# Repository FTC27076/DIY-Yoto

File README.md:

# DIY Yoto

A screen-free, kid-friendly audio player in the style of a Yoto. Put a card on top and it plays that card's stories or songs. It runs fully offline: no Wi-Fi, no app, no account. All audio lives on a micro SD card, and any 13.56 MHz RFID card or NFC sticker can become a card.

## Features

- Tap a card to play, lift it to pause, put it back to resume where it stopped
- Each card remembers which track it was on
- Two knobs: volume (press to pause) and track skip (press to restart the track)
- Volume cap for small ears
- Rechargeable LiPo with USB-C charging; play while charging
- Deep sleep after 5 minutes idle, wake with either knob
- Low-battery warning and safe shutdown

## Hardware

| Part | What it does |
|---|---|
| ESP32-S3-WROOM-1 (SMD) | Main controller |
| RC522 RFID reader | Reads the cards |
| Adafruit MAX98357A (#3006) | I2S amplifier, drives a 4–8 Ω 3 W speaker |
| Adafruit micro SD breakout (#4682) | Audio storage, 4-bit SDIO |
| TP4056 USB-C module (with protection) | Charges and protects the battery |
| MT3608 boost module | 5 V for the amp (set to 5.0 V before connecting!) |
| MCP1825S-3302E/AB (TO-220) | 3.3 V regulator for the logic |
| 2× EC11 rotary encoders | Volume and track controls |
| USB-C (J16) | Programming and Serial Monitor only |
| 3.7 V 2000 mAh LiPo (Adafruit #2011) | Power |

Everything except the ESP32 module is through-hole or a module on headers, so it's hand-solderable.
## BILL OF MATERIALS

Costs are in USD for one player. Most unit prices are estimates, so check them in each cart.

| Item | Qty | Supplier | Cost/item | Total Cost | link |
|---|---:|---|---:|---:|---|
| U2 – ESP32-S3-WROOM-1-N8R8 module (Espressif) | 1 | DigiKey | $4.50 | $4.50 | [link](https://www.digikey.ca/en/products/detail/espressif-systems/ESP32-S3-WROOM-1-N8R8/15295891) |
| U1 – MCP1825S-3302E/AB 3.3V LDO, TO-220 (Microchip) | 1 | DigiKey | $1.75 | $1.75 | [link](https://www.digikey.ca/en/products/result?keywords=MCP1825S-3302E%2FAB) |
| R1, R2 – 100k 1/4W resistor (Stackpole CF14JT100K, cut tape) | 2 | DigiKey | $0.10 | $0.20 | [link](https://www.digikey.ca/en/products/result?keywords=CF14JT100K) |
| R3–R8 – 10k 1/4W resistor (Stackpole CF14JT10K0, cut tape) | 6 | DigiKey | $0.10 | $0.60 | [link](https://www.digikey.ca/en/products/result?keywords=CF14JT10K0) |
| R9, R10 – 5.1k 1/4W resistor (Stackpole CF14JT5K10, cut tape) | 2 | DigiKey | $0.10 | $0.20 | [link](https://www.digikey.ca/en/products/detail/stackpole-electronics-inc/CF14JT5K10/1830367) |
| C1, C5 – 100µF 16V electrolytic (Panasonic EEU-FR1C101) | 2 | DigiKey | $0.40 | $0.80 | [link](https://www.digikey.ca/en/products/detail/panasonic-industry/EEU-FR1C101/2433525) |
| C2, C3, C9 – 10µF 25V ceramic, 5mm pitch (TDK FG28X5R1E106MRT06) | 3 | LCSC / JLC | $0.20 | $0.60 | [link](https://www.lcsc.com/product-detail/C1620216.html) |
| C4, C6, C7, C10 – 100nF 50V ceramic (KNSCHA 178MU0006) | 4 | LCSC / JLC | $0.03 | $0.12 | [link](https://www.lcsc.com/product-detail/C5632430.html) |
| C8 – 1µF 50V ceramic (KNSCHA 178MU0010) | 1 | LCSC / JLC | $0.05 | $0.05 | [link](https://www.lcsc.com/product-detail/C5632434.html) |
| SW2, SW3 – 6x6mm tactile switch, reset/boot (Omron B3F-1000) | 2 | DigiKey | $0.35 | $0.70 | [link](https://www.digikey.ca/en/products/detail/omron-electronics-inc-emc-div/B3F-1000/33150) |
| SW4, SW5 – rotary encoder with switch (Alps EC11E15244G1) | 2 | LCSC / JLC | $1.50 | $3.00 | [link](https://www.lcsc.com/product-detail/C370970.html) |
| J16 – USB-C receptacle, 16-pin (HRO TYPE-C-31-M-12) | 1 | LCSC / JLC | $0.25 | $0.25 | [link](https://www.lcsc.com/product-detail/C165948.html) |
| J3 – JST-PH 2-pin side-entry socket, battery (JST S2B-PH-K-S) | 1 | LCSC / JLC | $0.10 | $0.10 | [link](https://www.lcsc.com/product-detail/C173752.html) |
| J7 – JST-XH 2-pin socket, power switch (JST B2B-XH-A) | 1 | LCSC / JLC | $0.05 | $0.05 | [link](https://www.lcsc.com/product-detail/C158012.html) |
| MOD1 – 1x8 2.54mm female header (BOOMELE) | 1 | LCSC / JLC | $0.10 | $0.10 | [link](https://www.lcsc.com/product-detail/C27438.html) |
| J12 (M1) – TP4056 USB-C charger module with protection (pack of 5) | 1 | Amazon | $8.00 | $8.00 | [link](https://www.amazon.ca/s?k=TP4056+type-c+protection+module) |
| J13 (M2) – MT3608 boost module (pack of 5) | 1 | Amazon | $8.00 | $8.00 | [link](https://www.amazon.ca/s?k=MT3608+boost+module) |
| J14 (M3) – Adafruit MAX98357A I2S amp breakout (3006) | 1 | DigiKey | $5.95 | $5.95 | [link](https://www.digikey.ca/en/products/detail/adafruit-industries-llc/3006/6058477) |
| J15 (M4) – Adafruit micro SD SPI/SDIO breakout (4682) | 1 | DigiKey | $3.50 | $3.50 | [link](https://www.digikey.ca/en/products/detail/adafruit-industries-llc/4682/12822319) |
| MOD1 – RC522 RFID reader kit with card + fob (ProtoSupplies) | 1 | ProtoSupplies | $2.59 | $2.59 | [link](https://protosupplies.com/product/mfrc522-rfid-reader-key-card-and-key-ring/) |
| Header pins for M1/M2 – 1x40 break-away male header (BOOMELE) | 1 | LCSC / JLC | $0.15 | $0.15 | [link](https://www.lcsc.com/product-detail/C2337.html) |
| LiPo battery 3.7V 2000mAh with JST-PH (Adafruit 2011) | 1 | DigiKey | $12.50 | $12.50 | [link](https://www.digikey.ca/en/products/detail/adafruit-industries-llc/2011/6612469) |
| Speaker 40mm 4Ω 3W (Adafruit 3968) | 1 | DigiKey | $4.95 | $4.95 | [link](https://www.digikey.ca/en/products/detail/adafruit-industries-llc/3968/9745251) |
| Power switch – SPDT panel toggle 5A (E-Switch 100SP1T1B1M2QEH) | 1 | DigiKey | $4.50 | $4.50 | [link](https://www.digikey.ca/en/products/detail/e-switch/100SP1T1B1M2QEH/378821) |
| RFID cards – MIFARE Classic 1K (Adafruit 359) | 5 | DigiKey | $1.95 | $9.75 | [link](https://www.digikey.ca/en/products/detail/adafruit-industries-llc/359/5353589) |
| micro SD card 16–32GB (SanDisk / Samsung) | 1 | Amazon | $8.00 | $8.00 | [link](https://www.amazon.ca/s?k=sandisk+32gb+microsd) |
| Optional – JST-XH plug housing for J7 (JST XHP-2) | 0 | DigiKey | $0.10 | $0.00 | [link](https://www.digikey.ca/en/products/detail/jst-sales-america-inc/XHP-2/555485) |
| Optional – JST-XH crimp contacts (JST SXH-001T-P0.6, cut tape) | 0 | DigiKey | $0.10 | $0.00 | [link](https://www.digikey.ca/en/products/detail/jst-sales-america-inc/SXH-001T-P0.6/455-1135-1-ND/527370) |
| Parts subtotal | | | | $80.91 | |
| Tax (Ontario HST 13%) | | | | $13.77 | |
| **Grand total (USD)** | | | | **~$119.68** | |

### Pin map

| Function | GPIO |
|---|---|
| I2S BCLK / LRC / DIN | 5 / 6 / 7 |
| Amp enable (SD_MODE) | 8 |
| RC522 RST / SS / MOSI / SCK / MISO | 9 / 10 / 11 / 12 / 13 |
| SD CMD / CLK / D0 / D1 / D2 / D3 | 14 / 39 / 40 / 41 / 42 / 21 |
| Volume encoder A / B / push | 15 / 16 / 17 |
| Track encoder A / B / push | 18 / 4 / 2 |
| Battery sense (100k/100k divider) | 1 |
| USB D− / D+ | 19 / 20 |

## Repository contents

| Path | What's in it |
|---|---|
| `DiyYoto/DiyYoto.ino` | Arduino firmware |
| `DiyYoto/README.md` | Full firmware setup, SD card layout, controls and troubleshooting |
| `DiyYoto.pretty/` | Custom KiCad footprints for the four modules |
| `make_footprints.py` | Regenerates those footprints |

## Quick start

1. **Build the board.** Order the PCB, solder the parts, and set the MT3608 to 5.0 V with a multimeter *before* plugging in the amp.
2. **Flash the firmware.** In Arduino IDE 2, install the ESP32 core plus the MFRC522 and ESP32-audioI2S libraries. Set Board to *ESP32S3 Dev Module*, USB CDC On Boot to *Enabled*, and PSRAM to match your module. Switch the player on, plug USB into J16, hold BOOT, tap RESET, release BOOT, then upload.
3. **Prepare the SD card.** Format it FAT32 and create a `/cards` folder.
4. **Add a card.** Tap a blank card. The player creates `/cards/<card UID>/`. Copy MP3s into that folder (they play in alphabetical order), put the SD card back, and tap again.

## Images of final design

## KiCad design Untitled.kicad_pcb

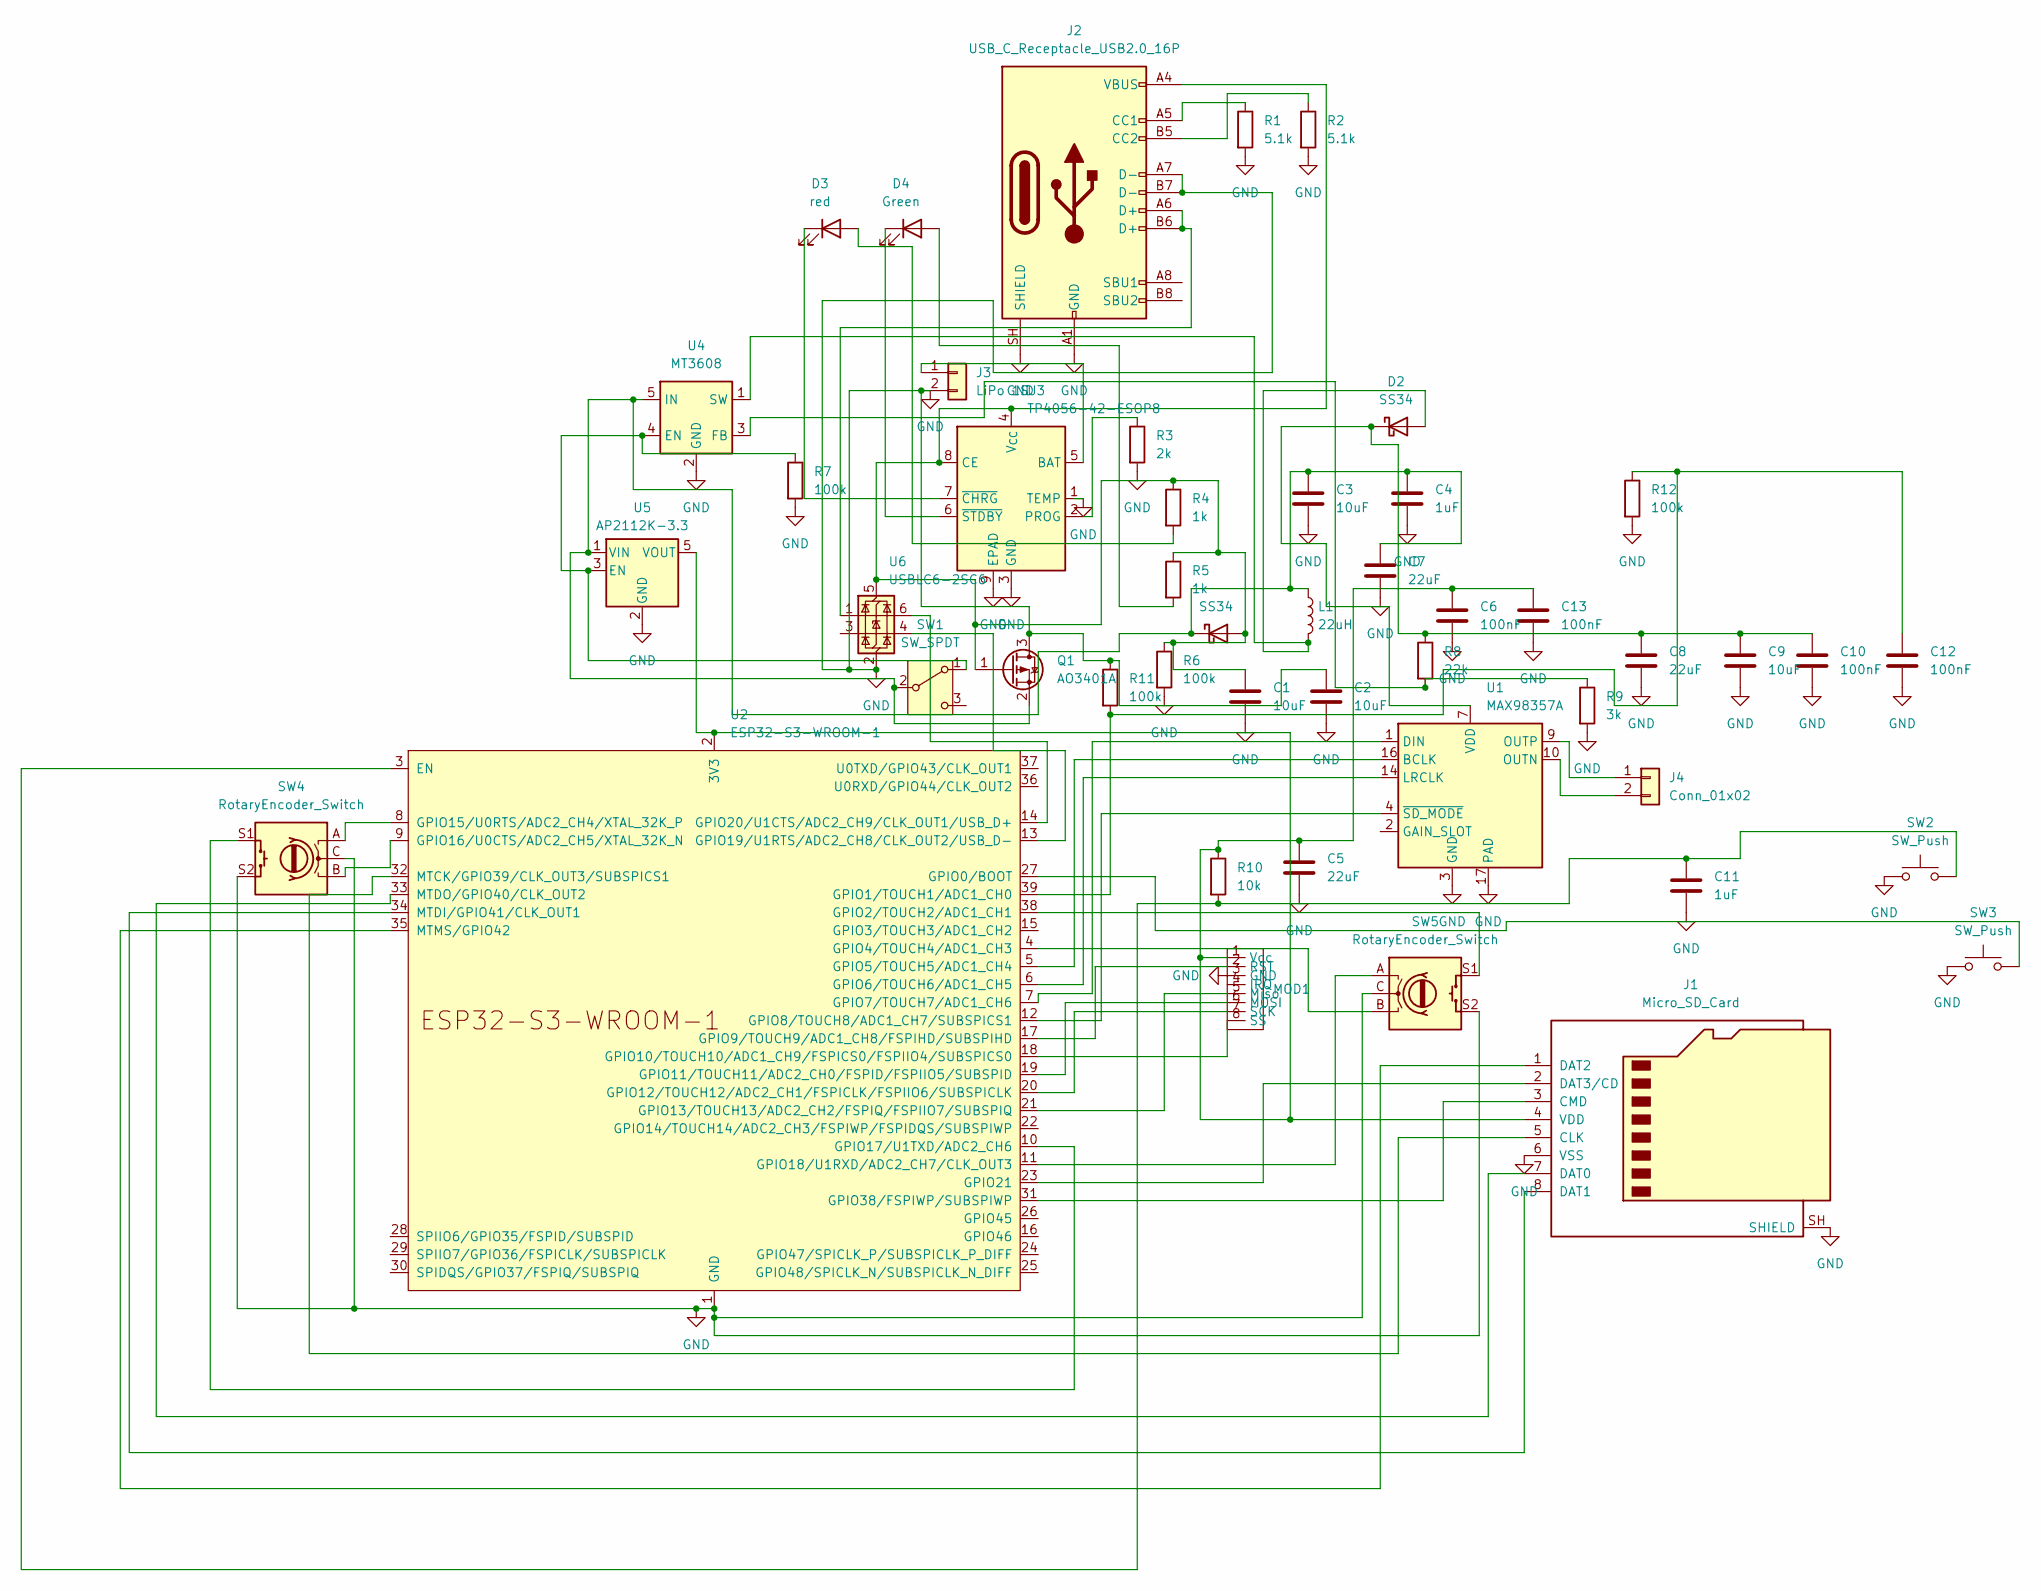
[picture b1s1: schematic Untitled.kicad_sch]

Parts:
C1, C2, C3, C9: 10uF; C_0603_1608Metric
C4, C11: 1uF; C_0603_1608Metric
C5, C7, C8: 22uF; C_0603_1608Metric
C6, C10, C12, C13: 100nF; C_0603_1608Metric
D1, D2: SS34; D_SMA
D3: red; LED_0805_2012Metric
D4: Green; LED_0805_2012Metric
J1: Micro_SD_Card; microSD_HC_Molex_104031-0811
J2: USB_C_Receptacle_USB2.0_16P; USB_C_Receptacle_HRO_TYPE-C-31-M-12
J3: LiPo 1S; JST_PH_S2B-PH-K_1x02_P2.00mm_Horizontal
J4: Conn_01x02; JST_PH_S2B-PH-K_1x02_P2.00mm_Horizontal
L1: 22uH; L_Bourns_SRN6045TA
MOD1: PinSocket_1x08_P2.54mm_Vertical
Q1: AO3401A; SOT-23
R1, R2: 5.1k; R_0603_1608Metric
R3: 2k; R_0603_1608Metric
R4, R5: 1k; R_0603_1608Metric
R6, R7, R11, R12: 100k; R_0603_1608Metric
R8: 22k; R_0603_1608Metric
R9: 3k; R_0603_1608Metric
R10: 10k; R_0603_1608Metric
SW1: SW_SPDT; SW_SPDT_PCM12
SW2, SW3: SW_Push; SW_SPST_TL3342
SW4, SW5: RotaryEncoder_Switch; RotaryEncoder_Alps_EC12E-Switch_Vertical_H20mm
U1: MAX98357A; TQFN-16-1EP_3x3mm_P0.5mm_EP1.23x1.23mm
U2: ESP32-S3-WROOM-1; ESP32-S3-WROOM-1ThermalVia0.3
U3: TP4056-42-ESOP8; SOIC-8-1EP_3.9x4.9mm_P1.27mm_EP2.41x3.3mm
U4: MT3608; SOT-23-6
U5: AP2112K-3.3; SOT-23-5
U6: USBLC6-2SC6; SOT-23-6

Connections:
GND: C1.2, C2.1, C2.2, C3.2, C4.2, C5.2, C6.2, C7.2, C8.2, C9.2, C10.2, C11.2, C12.2, C13.2, J1.6 (VSS), J1.SH (SHIELD), J2.A1 (GND), J2.A7 (D-), J2.A12 (GND), J2.B1 (GND), J2.B7 (D-), J2.B12 (GND), J2.SH (SHIELD), J3.2, MOD1.3 (GND), Q1.3 (D), R1.2, R2.2, R3.2, R6.2, R7.2, R9.2, R11.1, R12.2, SW2.1, SW3.1, SW4.C, SW4.S2, SW5.C, SW5.S2, U1.3 (GND), U1.11 (GND), U1.15 (GND), U1.17 (PAD), U2.1 (GND), U2.40 (GND), U2.41 (GND), U3.1 (TEMP), U3.3 (GND), U3.9 (EPAD), U4.2 (GND), U5.2 (GND), U6.2 (GND)
unnamed: C1.1, D1.2 (A), J2.A4 (VBUS), J2.A9 (VBUS), J2.B4 (VBUS), J2.B9 (VBUS), Q1.1 (G), R4.1, R5.1, R6.1, U3.4 (V_{CC}), U3.8 (CE), U6.5 (VBUS)
unnamed: C3.1, C4.1, C7.1, D1.1 (K), L1.1, Q1.2 (S), SW1.2 (B), U4.5 (IN), U5.1 (VIN)
unnamed: D2.2 (A), L1.2, U4.1 (SW)
unnamed: C8.1, C9.1, C10.1, D2.1 (K), R8.1, U1.7 (VDD), U1.8 (VDD)
unnamed: D3.2 (A), R4.2
unnamed: D3.1 (K), U3.7 (~CHRG)
unnamed: D4.2 (A), R5.2
unnamed: D4.1 (K), U3.6 (~STDBY)
unnamed: J1.5 (CLK), U2.32 (MTCK/GPIO39/CLK_OUT3/SUBSPICS1)
unnamed: J1.3 (CMD), U2.31 (GPIO38/FSPIWP/SUBSPIWP)
unnamed: J1.7 (DAT0), U2.33 (MTDO/GPIO40/CLK_OUT2)
unnamed: J1.8 (DAT1), U2.34 (MTDI/GPIO41/CLK_OUT1)
unnamed: J1.1 (DAT2), U2.35 (MTMS/GPIO42)
unnamed: J1.2 (DAT3/CD), U2.23 (GPIO21)
unnamed: C5.1, C6.1, C13.1, J1.4 (VDD), MOD1.1 (Vcc), R10.1, U2.2 (3V3), U5.5 (VOUT)
unnamed: J2.A5 (CC1), R1.1
unnamed: J2.B5 (CC2), R2.1
unnamed: J2.A6 (D+), J2.B6 (D+), U6.1 (I/O1)
unnamed: J3.1, U3.5 (BAT)
unnamed: J4.1, U1.9 (OUTP)
unnamed: J4.2, U1.10 (OUTN)
unnamed: MOD1.6 (MOSI), U2.19 (GPIO11/TOUCH11/ADC2_CH0/FSPID/FSPIIO5/S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)
unnamed: MOD1.5 (Miso), U2.21 (GPIO13/TOUCH13/ADC2_CH2/FSPIQ/FSPIIO7/S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)
unnamed: MOD1.2 (RST), U2.17 (GPIO9/TOUCH9/ADC1_CH8/FSPIHD/SUBSPIHD)
unnamed: MOD1.7 (SCK), U2.20 (GPIO12/TOUCH12/ADC2_CH1/FSPICLK/FSPIIO6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)
unnamed: MOD1.8 (SS), U2.18 (GPIO10/TOUCH10/ADC1_CH9/FSPICS0/FSPIIO4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)
unnamed: R7.1, SW1.1 (A), U4.4 (EN), U5.3 (EN)
unnamed: U1.16 (BCLK), U2.5 (GPIO5/TOUCH5/ADC1_CH4)
unnamed: U1.1 (DIN), U2.7 (GPIO7/TOUCH7/ADC1_CH6)
unnamed: U1.14 (LRCLK), U2.6 (GPIO6/TOUCH6/ADC1_CH5)
unnamed: U1.4 (~SD_MODE), U2.12 (GPIO8/TOUCH8/ADC1_CH7/SUBSPICS1)
unnamed: C11.1, R10.2, SW2.2, U2.3 (EN)
unnamed: SW3.2, U2.27 (GPIO0/BOOT)
unnamed: C12.1, R11.2, R12.1, U2.39 (GPIO1/TOUCH1/ADC1_CH0)
unnamed: SW5.S1, U2.38 (GPIO2/TOUCH2/ADC1_CH1)
unnamed: SW5.B, U2.4 (GPIO4/TOUCH4/ADC1_CH3)
unnamed: SW4.A, U2.8 (GPIO15/U0RTS/ADC2_CH4/XTAL_32K_P)
unnamed: SW4.B, U2.9 (GPIO16/U0CTS/ADC2_CH5/XTAL_32K_N)
unnamed: SW4.S1, U2.10 (GPIO17/U1TXD/ADC2_CH6)
unnamed: SW5.A, U2.11 (GPIO18/U1RXD/ADC2_CH7/CLK_OUT3)
unnamed: U2.13 (GPIO19/U1RTS/ADC2_CH8/CLK_OUT2/USB_D-), U6.4 (I/O2)
unnamed: U2.14 (GPIO20/U1CTS/ADC2_CH9/CLK_OUT1/USB_D+), U6.6 (I/O1)
unnamed: R3.1, U3.2 (PROG)
unnamed: R8.2, R9.1, U4.3 (FB)

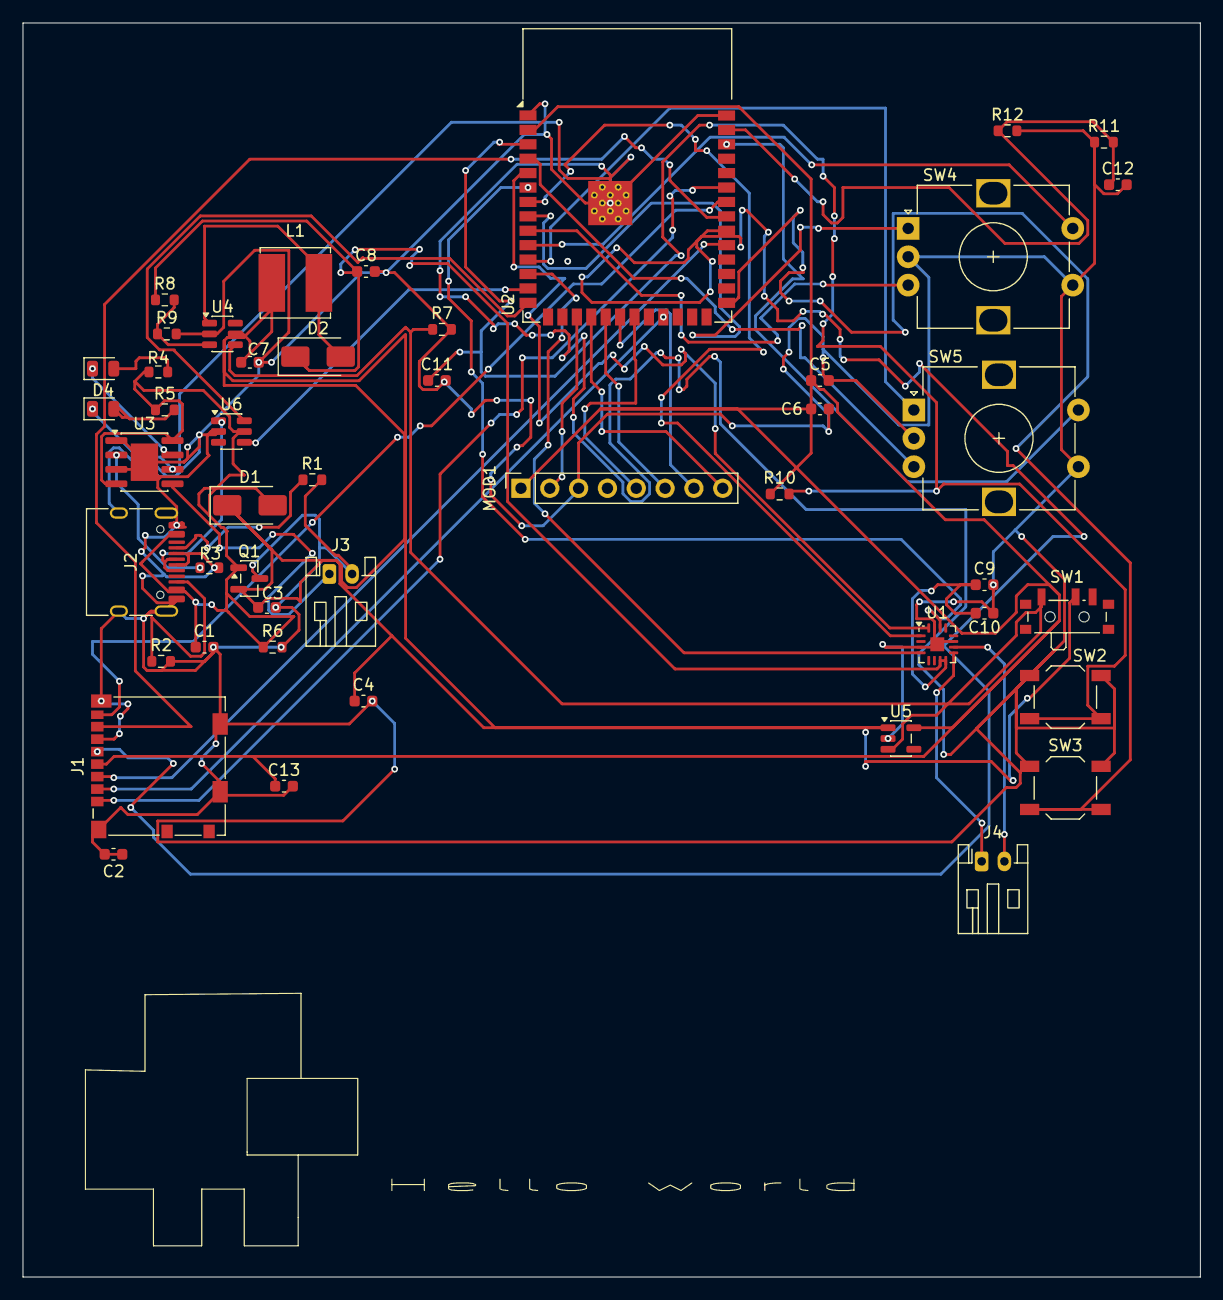
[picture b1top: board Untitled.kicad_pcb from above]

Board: 2 copper layers, 103.8 x 110.5 mm, 47 parts (0 on the bottom side), 45 nets.
